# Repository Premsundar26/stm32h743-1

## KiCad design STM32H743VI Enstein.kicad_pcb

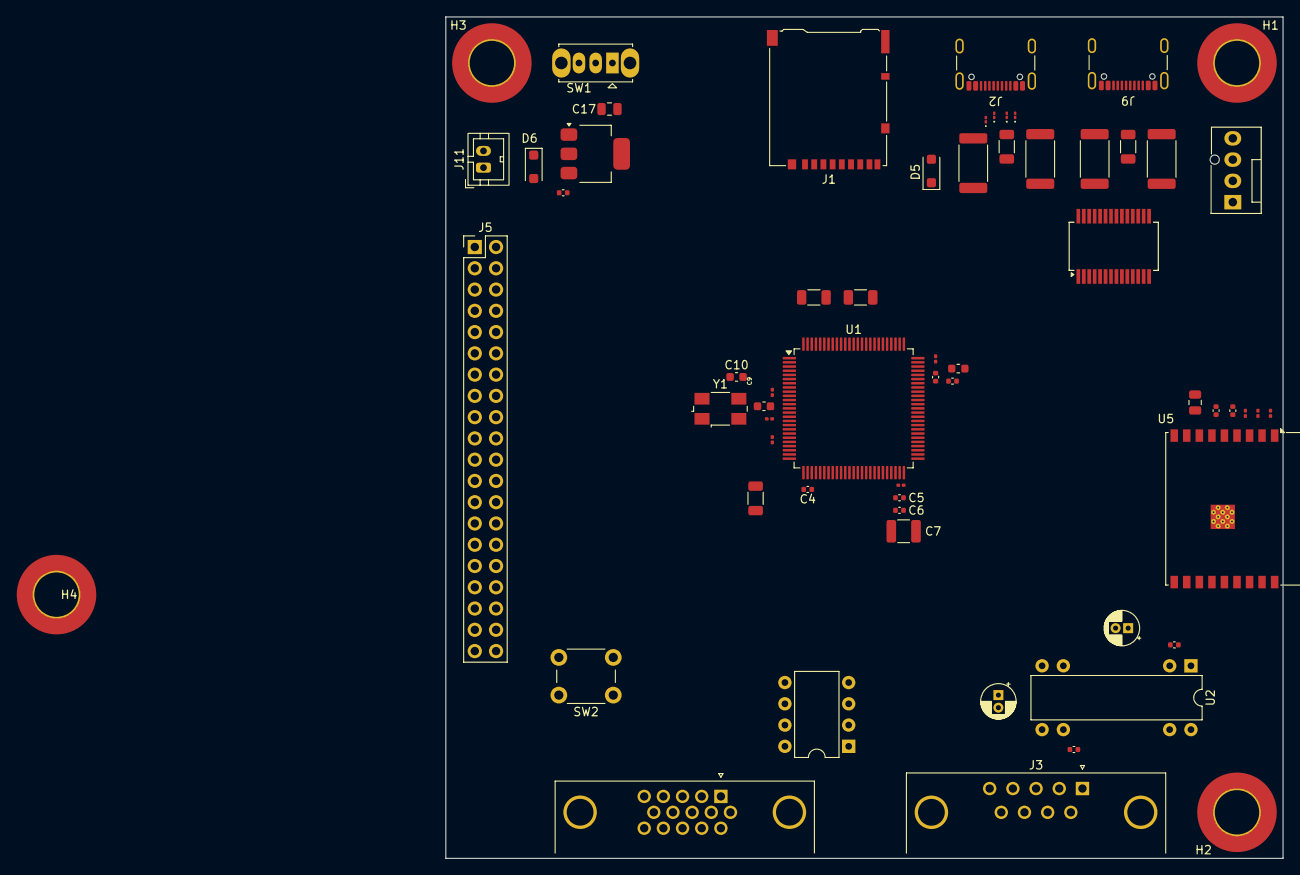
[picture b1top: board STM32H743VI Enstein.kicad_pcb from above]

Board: 4 copper layers, 100.0 x 100.5 mm, 62 parts (0 on the bottom side), 74 nets, no tracks yet.

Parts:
C1, C2, C3, C8, C13, C21, C22, C23: 100n; C_0201_0603Metric
C4, C5, C6, C14, C15, C18, C19, C24, C25: 1u; C_0402_1005Metric
C7: 4.7u; C_1210_3225Metric
C9, C10: 27p; C_0603_1608Metric
C11, C20: C_Polarized_Small; CP_Radial_D4.0mm_P1.50mm
C12, C17: 10u; C_0805_2012Metric
C16: 22u; C_0402_1005Metric
D1, D2, D3, D4: D; D_01005_0402Metric
D5, D6: MBR1020VL; D_SOD-123F
FB1: FerriteBead; L_0603_1608Metric
H1, H2, H3, H4: MountingHole; MountingHole_5.3mm_M5_ISO7380_Pad_TopBottom
J1: Micro_SD_Card; microSD_HC_Hirose_DM3AT-SF-PEJM5
J2, J9: USB_C_Receptacle_USB2.0_14P; USB_C_Receptacle_GCT_USB4105-xx-A_16P_TopMnt_Horizontal
J3: DE9_Plug; DSUB-9_Female_Horizontal_P2.77x2.84mm_EdgePinOffset4.94mm_H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
J4: Conn_01x04_Socket; FanPinHeader_1x04_P2.54mm_Vertical
J5: Conn_02x20_Top_Bottom; PinHeader_2x20_P2.54mm_Vertical
J8: DE15_Plug_HighDensity; DSUB-15-HD_Female_Horizontal_P2.29x1.90mm_EdgePinOffset3.03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
J11: Conn_01x02_Socket; TE_440054-2_1x02_P2.00mm_Vertical
R1, R2, R6, R7: 56k; R_2512_6332Metric
R3, R8, R10, R11: 1k5; R_1206_3216Metric
R9: 10k; R_1206_3216Metric
SW1: SW_SPDT; SW_Slide_SPDT_Straight_CK_OS102011MS2Q
SW2: SW_Push; SW_PUSH_6mm
U1: STM32H743VITx; LQFP-100_14x14mm_P0.5mm
U2: MAX232; DIP-8-16_W7.62mm
U3: AMS1117; SOT-223-3_TabPin2
U4: MCP2561-E-P; DIP-8_W7.62mm
U5: ESP32-C3; ESP32-C3-WROOM-02
U6: FT232RL; SSOP-28_5.3x10.2mm_P0.65mm
Y1: Crystal_GND24; Crystal_SMD_0603-4Pin_6.0x3.5mm

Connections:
+3V3: C1.1, C2.1, C3.1, C4.1, C5.1, C6.1, C7.1, C12.1, C13.1, C14.1, C15.1, C18.2, C21.1, C22.1, C23.1, C24.1, C25.1, FB1.1, FB1.2, J1.4 (VDD), J4.1, J5.9, J8.13, R1.1, R2.1, R3.2, R6.1, R7.1, R8.2, R9.1, R10.2, R11.2, SW1.3 (C), U1.6 (VBAT), U1.11 (VDD), U1.21 (VDDA), U1.27 (VDD), U1.50 (VDD), U1.75 (VDD), U1.100 (VDD), U4.3 (VDD), U6.4 (VCCIO), U6.20 (VCC)
CAN_RX: J5.17, U1.51 (PB12), U4.1 (TXD)
CAN_TX: J5.18, U1.52 (PB13), U4.4 (RXD)
CLK: J1.5 (CLK), U1.16 (PC1)
CMD: J1.3 (CMD), U1.22 (PA0)
D0: J1.7 (DAT0), U1.53 (PB14)
D1: J1.8 (DAT1), U1.54 (PB15)
D2: J1.1 (DAT2), U1.89 (PB3)
D3: J1.2 (DAT3/CD), U1.90 (PB4)
ESP_UART_RX: J5.1, U1.37 (PE7)
ESP_UART_TX: J5.2, U1.38 (PE8)
GND: C1.2, C2.2, C3.2, C4.2, C5.2, C6.2, C7.2, C9.2, C10.2, C13.2, C14.2, C15.2, C16.2, C17.2, C19.2, J1.6 (VSS), J2.A1 (GND), J2.A12 (GND), J2.B1 (GND), J2.B12 (GND), J2.S1 (SHIELD), J3.5, J4.4, J5.10, J8.7, J9.A1 (GND), J9.A12 (GND), J9.B1 (GND), J9.B12 (GND), J9.S1 (SHIELD), J11.2, SW1.1 (A), SW2.1, U1.10 (VSS), U1.19 (VSSA), U1.26 (VSS), U1.49 (VSS), U1.74 (VSS), U1.99 (VSS), U3.1 (ADJ), U4.2 (VSS), U6.7 (GND), U6.18 (GND), U6.21 (GND), U6.25 (AGND), U6.26 (TEST)
GPIO_1: J5.27, U1.40 (PE10)
GPIO_2: J5.28, U1.41 (PE11)
GPIO_3: J5.29, U1.42 (PE12)
GPIO_4: J5.30, U1.43 (PE13)
GPIO_5: J5.31, U1.44 (PE14)
GPIO_6: J5.32, U1.45 (PE15)
GPIO_7: J5.33, U1.81 (PD0)
GPIO_8: J5.34, U1.82 (PD1)
I2C2_SCL: J5.8, U1.46 (PB10)
I2C2_SDA: J5.7, U1.47 (PB11)
I2C3_SCL: J5.13, U1.67 (PA8)
I2C3_SDA: J5.14, U1.66 (PC9)
I2C4_SCL: J5.15, U1.59 (PD12)
I2C4_SDA: J5.16, U1.60 (PD13)
I2C_CLK: J5.11, J8.1, R11.1, U1.92 (PB6)
I2C_SDA: J5.12, J8.2, R10.1, U1.93 (PB7)
MISO: J5.25, J8.4, U1.30 (PA6)
MOSI: J5.26, J8.3, U1.31 (PA7)
NRST: C8.1, R9.2, U1.14 (NRST)
unnamed: C8.2, SW2.2
unnamed: D1.2 (A), J2.A7 (D-)
unnamed: D2.2 (A), J2.B7 (D-)
unnamed: D3.2 (A), D4.2 (A), J2.A6 (D+), J2.B6 (D+), R3.1
unnamed: D6.2 (A), J11.1
unnamed: J2.A5 (CC1), R1.2
unnamed: J2.B5 (CC2), R2.2
unnamed: J9.A5 (CC1), R6.2
unnamed: J9.B5 (CC2), R7.2
unnamed: SW1.2 (B), U1.94 (BOOT0)
unnamed: C9.1, U1.12 (PH0), Y1.1
unnamed: C10.1, U1.13 (PH1), Y1.3
unnamed: C11.1, U2.1 (C1+)
unnamed: C11.2, U2.3 (C1-)
unnamed: C20.1, U2.4 (C2+)
unnamed: C20.2, U2.5 (C2-)
unnamed: C18.1, U2.2 (VS+)
unnamed: C19.1, U2.6 (VS-)
unnamed: C17.1, U3.2 (VO)
unnamed: J8.14, U4.7 (CANH)
unnamed: J8.15, U4.6 (CANL)
unnamed: C12.2, C21.2, C22.2, C23.2, C24.2, C25.2, U5.2 (VDD3P3), U5.3 (VDD3P3), U5.11 (VDD3P3_RTC), U5.17 (VDD3P3_CPU), U5.18 (VDD_SPI)
unnamed: Y1.2, Y1.4
RS232_RX: J5.3, U1.83 (PD2)
RS232_TX: J5.4, U1.80 (PC12)
SPI2_CS: J5.20, U1.2 (PE3)
SPI2_MISO: J5.21, U1.4 (PE5)
SPI2_MOSI: J5.22, U1.5 (PE6)
SPI2_SCK: J5.19, U1.1 (PE2)
SPI_CS: J5.24, J8.6, U1.28 (PA4)
SPI_SCK: J5.23, J8.5, U1.29 (PA5)
SWDIO: J4.2, U1.72 (PA13)
SW_CLK: J4.3, U1.76 (PA14)
UART_RX: J5.5, J8.12, U1.25 (PA3)
UART_TX: J5.6, J8.11, U1.24 (PA2)
USB-UART RX: U1.97 (PE0), U6.1 (TXD)
USB-UART TX: U1.98 (PE1), U6.5 (RXD)
USB_COMM DM: J9.A7 (D-), J9.B7 (D-), U6.16 (USBD-)
USB_COMM DP: J9.A6 (D+), J9.B6 (D+), R8.1, U6.15 (USBD+)
USB_SDCARD DM: D1.1 (K), D2.1 (K), U1.70 (PA11)
USB_SDCARD DP: D3.1 (K), D4.1 (K), U1.71 (PA12)
VBUS: D5.2 (A), J2.A4 (VBUS), J2.A9 (VBUS), J2.B4 (VBUS), J2.B9 (VBUS), J9.A4 (VBUS), J9.A9 (VBUS), J9.B4 (VBUS), J9.B9 (VBUS)
V_INPUT: C16.1, D5.1 (K), D6.1 (K), U3.3 (VI)

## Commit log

2024-12-19 PCB starting stage
2024-12-20 enstien
